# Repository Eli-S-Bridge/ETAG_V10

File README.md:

# ETAG_V10
ETAG arduino code and assembly files for the ETAG RFID reader version 10.

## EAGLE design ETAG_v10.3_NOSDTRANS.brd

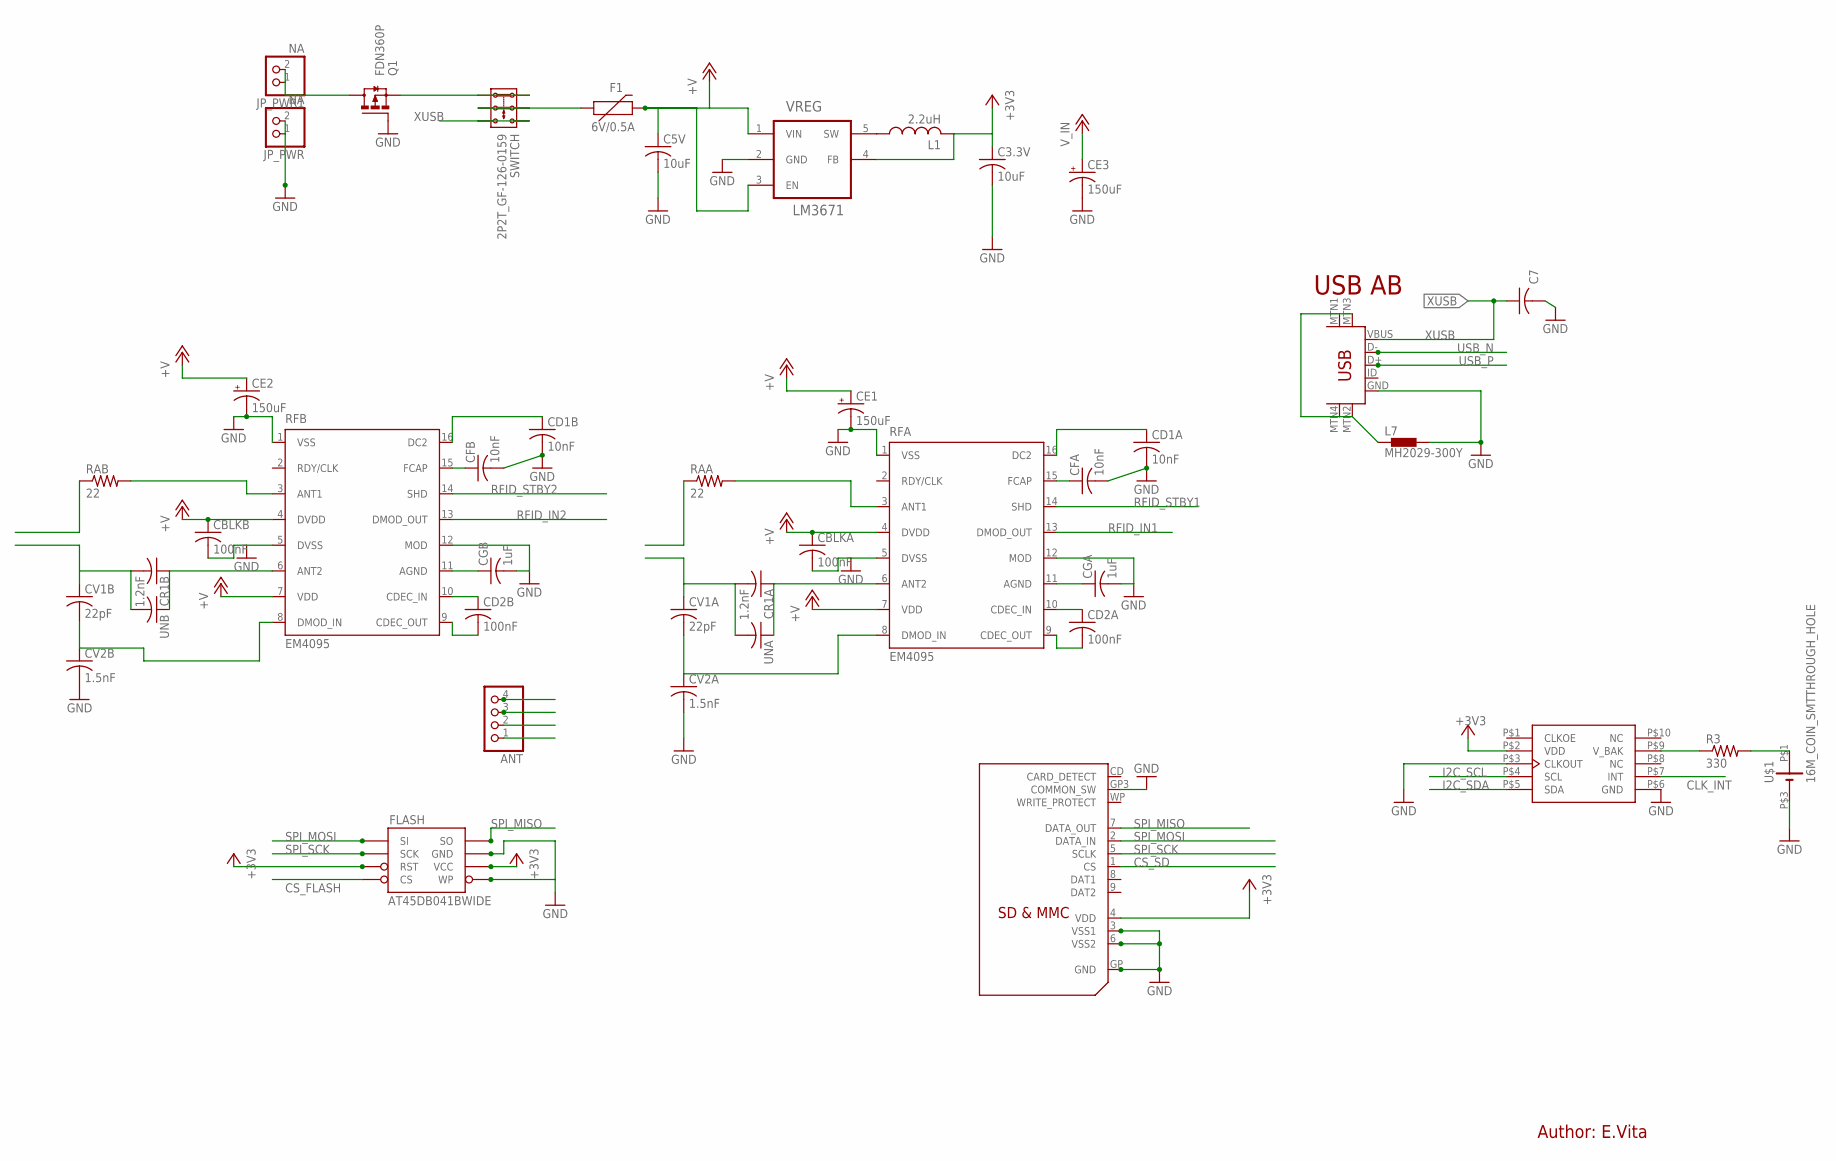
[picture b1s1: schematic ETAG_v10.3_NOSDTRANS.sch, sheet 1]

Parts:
ANT: PINHD-1X4; 1X04
C3.3V, C5V: 10uF; C0805
C7: 10nF; C0603-ROUND
CBLKA: 100nF; C0603-ROUND
CBLKB: 100nF; C0603-ROUND
CD1A, CD1B: 10nF; C0603-ROUND
CD2A, CD2B: 100nF; C0603-ROUND
CE1, CE2, CE3: 150uF; PANASONIC_C
CFA: 10nF; C0603-ROUND
CFB: 10nF; C0603-ROUND
CGA: 1uF; C0603-ROUND
CGB: 1uF; C0603-ROUND
CR1A, CR1B: 1.2nF; C0603-ROUND
CV1A, CV1B: 22pF; C0603-ROUND
CV2A, CV2B: 1.5nF; C0603-ROUND
F1: 6V/0.5A; 1206
FLASH: AT45DB041BWIDE; SO08WIDE
JP_PWR, JP_PWR1: NA; 1X02
L1: 2.2uH; SMT_COIL_INDUCTOR_4X4MM
L7: MH2029-300Y; C0805K
Q1: FDN360P; SUPER-SOT3
R3: 330; C0603-ROUND
RAA: 22; R0805
RAB: 22; R0805
RFA: EM4095; SO16
RFB: EM4095; SO16
RTC: MC-RTC-RV-3029-C3-I2C; MC-RTC-C3_SPECIAL
SD: SDMMC06132; 06132
SWITCH: 2P2T_GF-126-0159
U$1: 16M_COIN_SMTTHROUGH_HOLE; 16_MM_THROUGH_HOLE
UNA: C-US; C0603-ROUND
UNB: C-US; C0603-ROUND
USB: USB-MINIB-5PIN; USB-MINIB
VREG: LM3671; SOT23-5L

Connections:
2GND: L7.1, USB.MTN1 (MTN2), USB.MTN2 (MTN3), USB.MTN3 (MTN1), USB.MTN4
12_IN: JP_PWR1.1, JP_PWR1.2, Q1.3 (D)
+3V3: C3.3V.1, FLASH.3 (RST), FLASH.6 (VCC), L1.P$2 (2), RTC.P$2 (VDD), SD.4 (VDD), VREG.4 (FB); also elsewhere on the board
AANT: ANT.4, RAA.1
BANT: ANT.2, RAB.1
CLK_INT: RTC.P$7 (INT); also elsewhere on the board
CS_FLASH: FLASH.4 (CS); also elsewhere on the board
CS_SD: SD.1 (CS); also elsewhere on the board
CVA: ANT.3, CR1A.2, CV1A.1, UNA.2
CVB: ANT.1, CR1B.2, CV1B.1, UNB.2
GND: C3.3V.2, C5V.2, C7.2, CBLKA.2, CBLKB.2, CD1A.2, CD1B.2, CE1.-, CE2.-, CE3.-, CFA.2, CFB.2, CGA.2, CGB.2, CV2A.2, CV2B.2, FLASH.5 (WP), FLASH.7 (GND), JP_PWR.1, JP_PWR.2, L7.2, Q1.1 (G), RFA.1 (VSS), RFA.5 (DVSS), RFA.12 (MOD), RFB.1 (VSS), RFB.5 (DVSS), RFB.12 (MOD), RTC.P$3 (CLKOUT), RTC.P$6 (GND), SD.3 (VSS1), SD.6 (VSS2), SD.GP (GND), SD.GP3 (COMMON_SW), U$1.P$3 (-), USB.GND, VREG.2 (GND); also elsewhere on the board
I2C_SCL: RTC.P$4 (SCL); also elsewhere on the board
I2C_SDA: RTC.P$5 (SDA); also elsewhere on the board
unnamed: CFB.1, RFB.15 (FCAP)
unnamed: CGB.1, RFB.11 (AGND)
unnamed: CFA.1, RFA.15 (FCAP)
unnamed: CGA.1, RFA.11 (AGND)
unnamed: CD1A.1, RFA.16 (DC2)
unnamed: CR1B.1, RFB.6 (ANT2), UNB.1
unnamed: CV1B.2, CV2B.1, RFB.8 (DMOD_IN)
unnamed: CD1B.1, RFB.16 (DC2)
unnamed: F1.1, SWITCH.P2A (2.1), SWITCH.P2B (2.2)
unnamed: CD2B.2, RFB.9 (CDEC_OUT)
unnamed: CR1A.1, RFA.6 (ANT2), UNA.1
unnamed: CV1A.2, CV2A.1, RFA.8 (DMOD_IN)
unnamed: CD2B.1, RFB.10 (CDEC_IN)
unnamed: RAB.2, RFB.3 (ANT1)
unnamed: Q1.2 (S), SWITCH.P1A (1.1), SWITCH.P1B (1.2)
unnamed: CD2A.2, RFA.9 (CDEC_OUT)
unnamed: CD2A.1, RFA.10 (CDEC_IN)
unnamed: RAA.2, RFA.3 (ANT1)
unnamed: R3.1, RTC.P$9 (V_BAK)
unnamed: R3.2, U$1.P$1 (+)
RFID_IN1: RFA.13 (DMOD_OUT); also elsewhere on the board
RFID_IN2: RFB.13 (DMOD_OUT); also elsewhere on the board
RFID_STBY1: RFA.14 (SHD); also elsewhere on the board
RFID_STBY2: RFB.14 (SHD); also elsewhere on the board
SPI_MISO: FLASH.8 (SO), SD.7 (DATA_OUT); also elsewhere on the board
SPI_MOSI: FLASH.1 (SI), SD.2 (DATA_IN); also elsewhere on the board
SPI_SCK: FLASH.2 (SCK), SD.5 (SCLK); also elsewhere on the board
SW: L1.P$1 (1), VREG.5 (SW)
USB_N: USB.D-; also elsewhere on the board
USB_P: USB.D+; also elsewhere on the board
V_IN: C5V.1, CBLKA.1, CBLKB.1, CE1.+, CE2.+, CE3.+, F1.2, RFA.4 (DVDD), RFA.7 (VDD), RFB.4 (DVDD), RFB.7 (VDD), VREG.1 (VIN), VREG.3 (EN); also elsewhere on the board
XUSB: C7.1, SWITCH.P3A (3.1), SWITCH.P3B (3.2), USB.VBUS

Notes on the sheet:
USB AB
Author: E.Vita

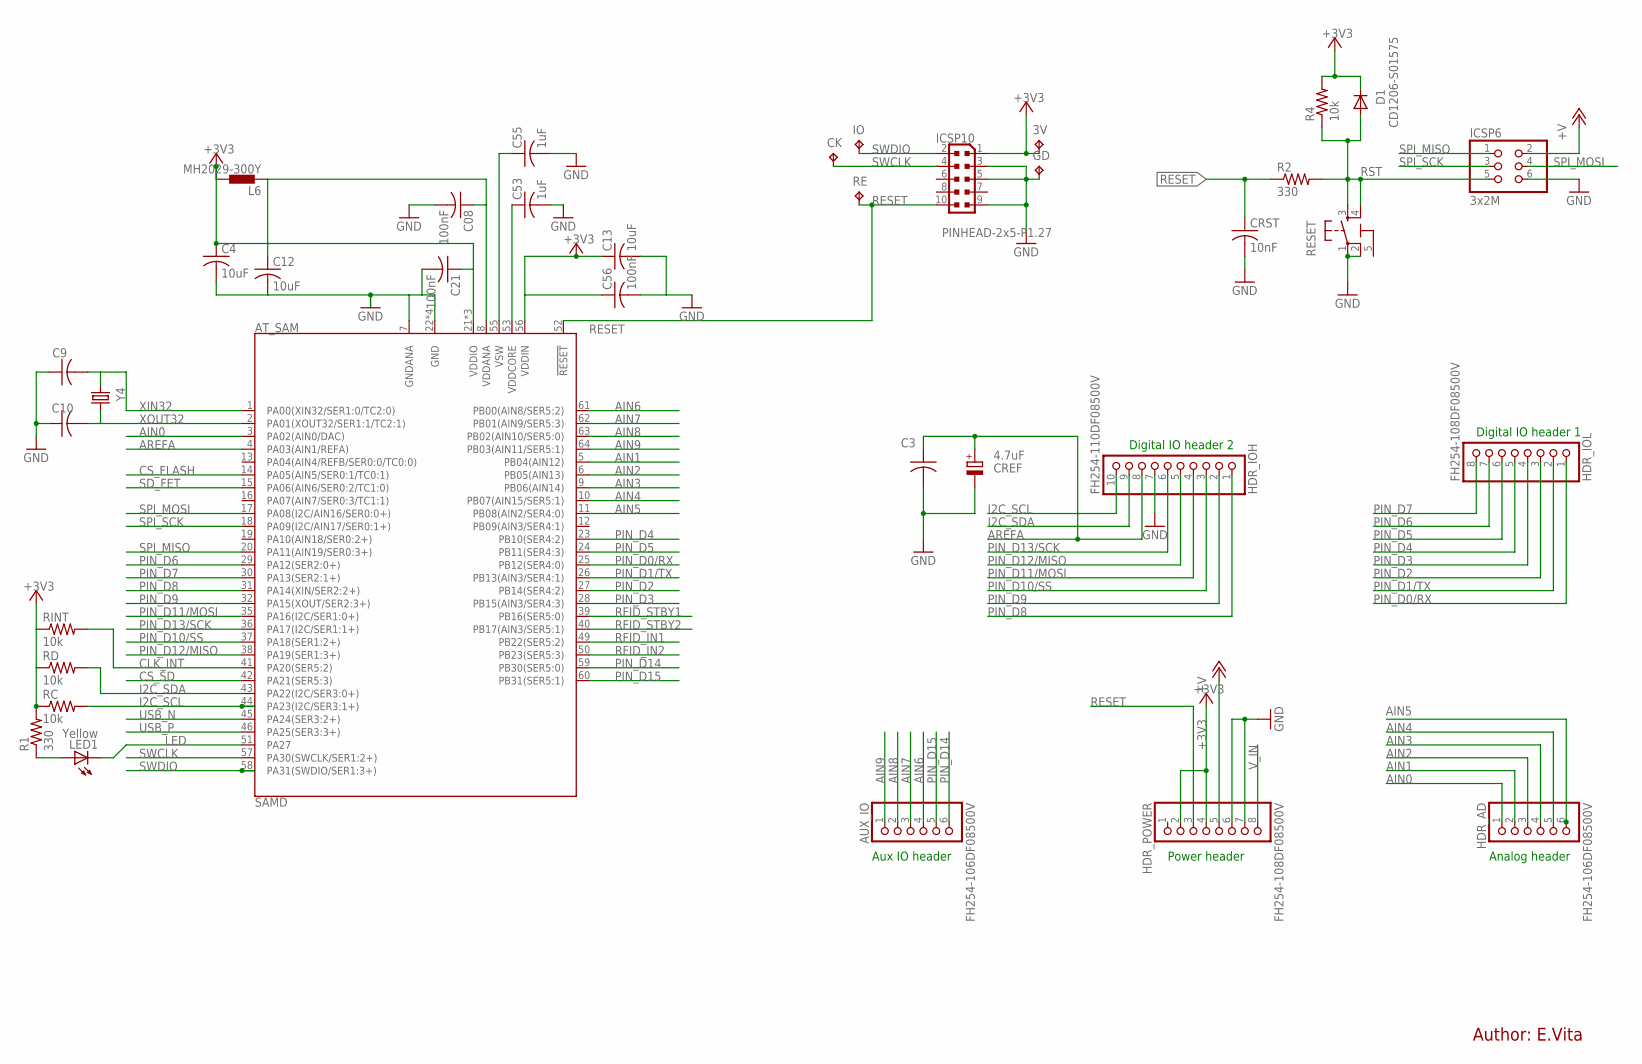
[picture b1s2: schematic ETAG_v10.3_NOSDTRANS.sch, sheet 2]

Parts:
3V: TPTP12R; TP12R
AT_SAM: SAMD; TQFP_10MM_0.5PITCH
AUX_IO: FH254-106DF08500V; 1X06
C3, C08, C21, C56: 100nF; C0603-ROUND
C4, C12, C13: 10uF; C0805
C9, C10: 22pF; C0603-ROUND
C53, C55: 1uF; C0603-ROUND
CK: TPTP12R; TP12R
CREF: 4.7uF; SMC_A
CRST: 10nF; C0603-ROUND
D1: CD1206-S01575; MINIMELF
GD: TPTP12R; TP12R
HDR_AD: FH254-106DF08500V; 1X06
HDR_IOH: FH254-110DF08500V; 1X10
HDR_IOL: FH254-108DF08500V; 1X08
HDR_POWER: FH254-108DF08500V; 1X08
ICSP6: 3x2M; 2X03
ICSP10: PINHEAD-2x5-P1.27; PINHEAD_2X05_127
IO: TPTP12R; TP12R
L6: MH2029-300Y; C0805K
LED1: Yellow; CHIPLED_0805
R1, R2: 330; C0603-ROUND
R4: 10k; C0603-ROUND
RC: 10k; C0603-ROUND
RD: 10k; C0603-ROUND
RE: TPTP12R; TP12R
RESET: TS42031-160R-TR-7260; TS42
RINT: 10k; C0603-ROUND
Y4: 32,768Khz; RESONATOR_EPSON_FC_145

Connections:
5-GND: RESET.5 (5-GND)
+3V3: 3V.TP, AT_SAM.21 (VDDIO), AT_SAM.34 (VDDIO), AT_SAM.48 (VDDIO), AT_SAM.56 (VDDIN), C4.1, C13.1, C21.1, C56.1, D1.C, HDR_POWER.2, HDR_POWER.4, ICSP10.1, L6.2, R1.2, R4.2, RC.1, RD.1, RINT.1; also elsewhere on the board
AIN0: AT_SAM.3 (PA02(AIN0/DAC)), HDR_AD.1
AIN1: AT_SAM.5 (PB04(AIN12)), HDR_AD.2
AIN2: AT_SAM.6 (PB05(AIN13)), HDR_AD.3
AIN3: AT_SAM.9 (PB06(AIN14)), HDR_AD.4
AIN4: AT_SAM.10 (PB07(AIN15/SER5:1)), HDR_AD.5
AIN5: AT_SAM.11 (PB08(AIN2/SER4:0)), HDR_AD.6
AIN6: AT_SAM.61 (PB00(AIN8/SER5:2)), AUX_IO.4
AIN7: AT_SAM.62 (PB01(AIN9/SER5:3)), AUX_IO.3
AIN8: AT_SAM.63 (PB02(AIN10/SER5:0)), AUX_IO.2
AIN9: AT_SAM.64 (PB03(AIN11/SER5:1)), AUX_IO.1
AREFA: AT_SAM.4 (PA03(AIN1/REFA)), C3.1, CREF.+, HDR_IOH.8
CLK_INT: AT_SAM.41 (PA20(SER5:2)), RINT.2; also elsewhere on the board
CS_FLASH: AT_SAM.14 (PA05(AIN5/SER0:1/TC0:1)); also elsewhere on the board
CS_SD: AT_SAM.42 (PA21(SER5:3)); also elsewhere on the board
GND: AT_SAM.7 (GNDANA), AT_SAM.22 (GND), AT_SAM.33 (GND), AT_SAM.47 (GND), AT_SAM.54 (GND), C3.2, C4.2, C08.2, C9.1, C10.1, C12.2, C13.2, C21.2, C53.2, C55.2, C56.2, CREF.-, CRST.2, GD.TP, HDR_IOH.7, HDR_POWER.6, HDR_POWER.7, ICSP6.6, ICSP10.3, ICSP10.5, ICSP10.9, RESET.1, RESET.2; also elsewhere on the board
I2C_SCL: AT_SAM.44 (PA23(I2C/SER3:1+)), HDR_IOH.10, RC.2; also elsewhere on the board
I2C_SDA: AT_SAM.43 (PA22(I2C/SER3:0+)), HDR_IOH.9, RD.2; also elsewhere on the board
LED: AT_SAM.51 (PA27), LED1.C
unnamed: LED1.A, R1.1
unnamed: AT_SAM.53 (VDDCORE), C53.1
unnamed: AT_SAM.55 (VSW), C55.1
PIN_D0/RX: AT_SAM.25 (PB12(SER4:0)), HDR_IOL.1
PIN_D1/TX: AT_SAM.26 (PB13(AIN3/SER4:1)), HDR_IOL.2
PIN_D2: AT_SAM.27 (PB14(SER4:2)), HDR_IOL.3
PIN_D3: AT_SAM.28 (PB15(AIN3/SER4:3)), HDR_IOL.4
PIN_D4: AT_SAM.23 (PB10(SER4:2)), HDR_IOL.5
PIN_D5: AT_SAM.24 (PB11(SER4:3)), HDR_IOL.6
PIN_D6: AT_SAM.29 (PA12(SER2:0+)), HDR_IOL.7
PIN_D7: AT_SAM.30 (PA13(SER2:1+)), HDR_IOL.8
PIN_D8: AT_SAM.31 (PA14(XIN/SER2:2+)), HDR_IOH.1
PIN_D9: AT_SAM.32 (PA15(XOUT/SER2:3+)), HDR_IOH.2
PIN_D10/SS: AT_SAM.37 (PA18(SER1:2+)), HDR_IOH.3
PIN_D11/MOSI: AT_SAM.35 (PA16(I2C/SER1:0+)), HDR_IOH.4
PIN_D12/MISO: AT_SAM.38 (PA19(SER1:3+)), HDR_IOH.5
PIN_D13/SCK: AT_SAM.36 (PA17(I2C/SER1:1+)), HDR_IOH.6
PIN_D14: AT_SAM.59 (PB30(SER5:0)), AUX_IO.6
PIN_D15: AT_SAM.60 (PB31(SER5:1)), AUX_IO.5
RESET: AT_SAM.52 (!RESET!), CRST.1, HDR_POWER.3, ICSP10.10, R2.1, RE.TP
RFID_IN1: AT_SAM.49 (PB22(SER5:2)); also elsewhere on the board
RFID_IN2: AT_SAM.50 (PB23(SER5:3)); also elsewhere on the board
RFID_STBY1: AT_SAM.39 (PB16(SER5:0)); also elsewhere on the board
RFID_STBY2: AT_SAM.40 (PB17(AIN3/SER5:1)); also elsewhere on the board
RST: D1.A, ICSP6.5, R2.2, R4.1, RESET.3, RESET.4
SD_FET: AT_SAM.15 (PA06(AIN6/SER0:2/TC1:0))
SPI_MISO: AT_SAM.20 (PA11(AIN19/SER0:3+)), ICSP6.1; also elsewhere on the board
SPI_MOSI: AT_SAM.17 (PA08(I2C/AIN16/SER0:0+)), ICSP6.4; also elsewhere on the board
SPI_SCK: AT_SAM.18 (PA09(I2C/AIN17/SER0:1+)), ICSP6.3; also elsewhere on the board
SWCLK: AT_SAM.57 (PA30(SWCLK/SER1:2+)), CK.TP, ICSP10.4
SWDIO: AT_SAM.58 (PA31(SWDIO/SER1:3+)), ICSP10.2, IO.TP
USB_N: AT_SAM.45 (PA24(SER3:2+)); also elsewhere on the board
USB_P: AT_SAM.46 (PA25(SER3:3+)); also elsewhere on the board
VDDANA: AT_SAM.8 (VDDANA), C08.1, C12.1, L6.1
V_IN: HDR_POWER.5, HDR_POWER.8, ICSP6.2; also elsewhere on the board
XIN32: AT_SAM.1 (PA00(XIN32/SER1:0/TC2:0)), C9.2, Y4.P$1 (1)
XOUT32: AT_SAM.2 (PA01(XOUT32/SER1:1/TC2:1)), C10.2, Y4.P$2 (2)

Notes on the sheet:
Author: E.Vita
Digital IO header 2
Digital IO header 1
Analog header
Power header
Aux IO header

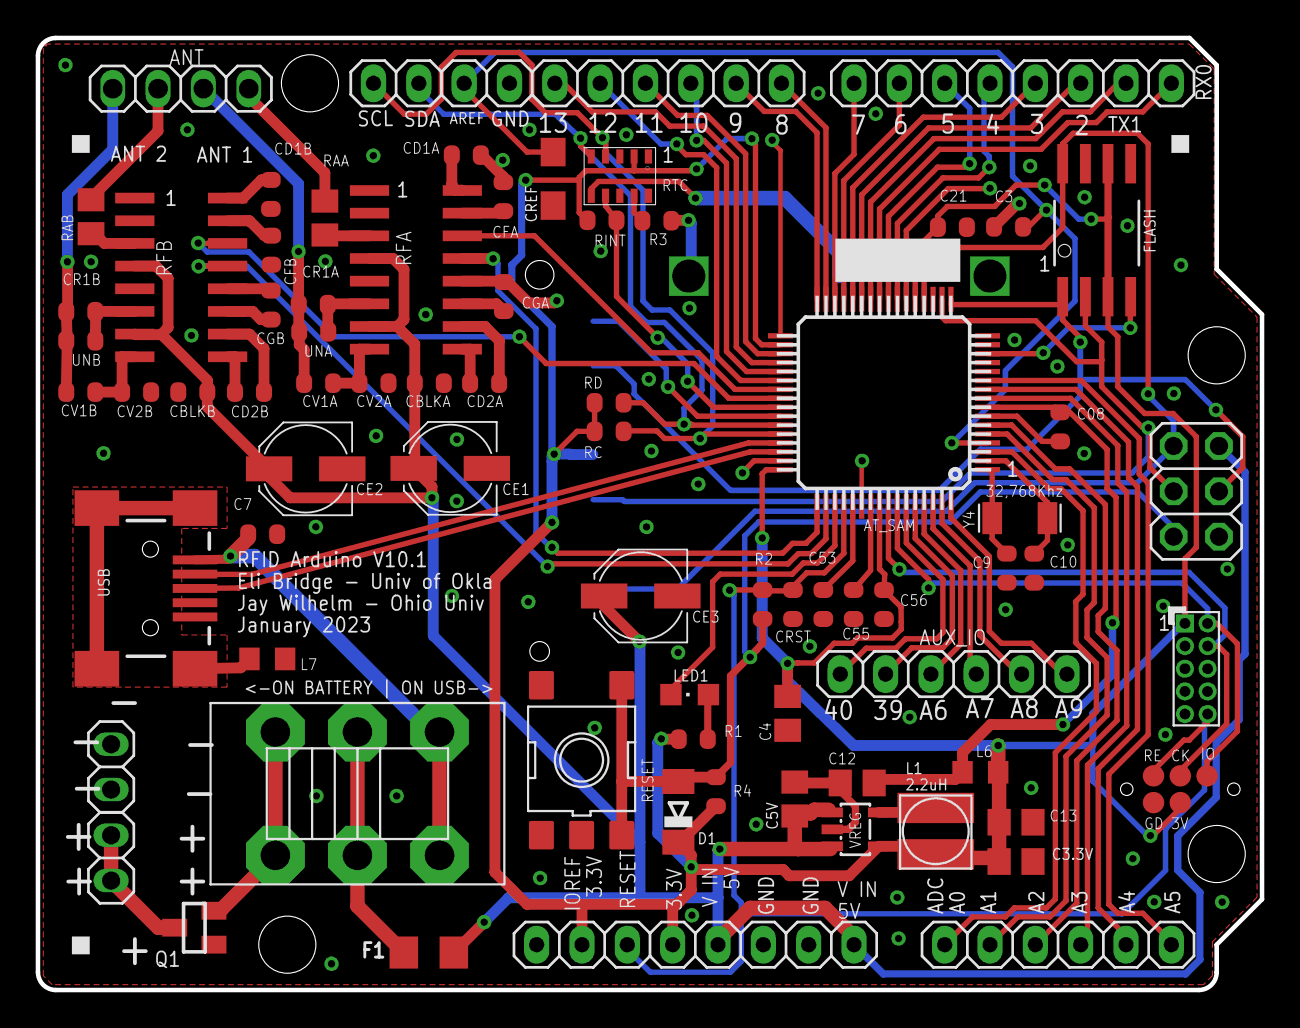
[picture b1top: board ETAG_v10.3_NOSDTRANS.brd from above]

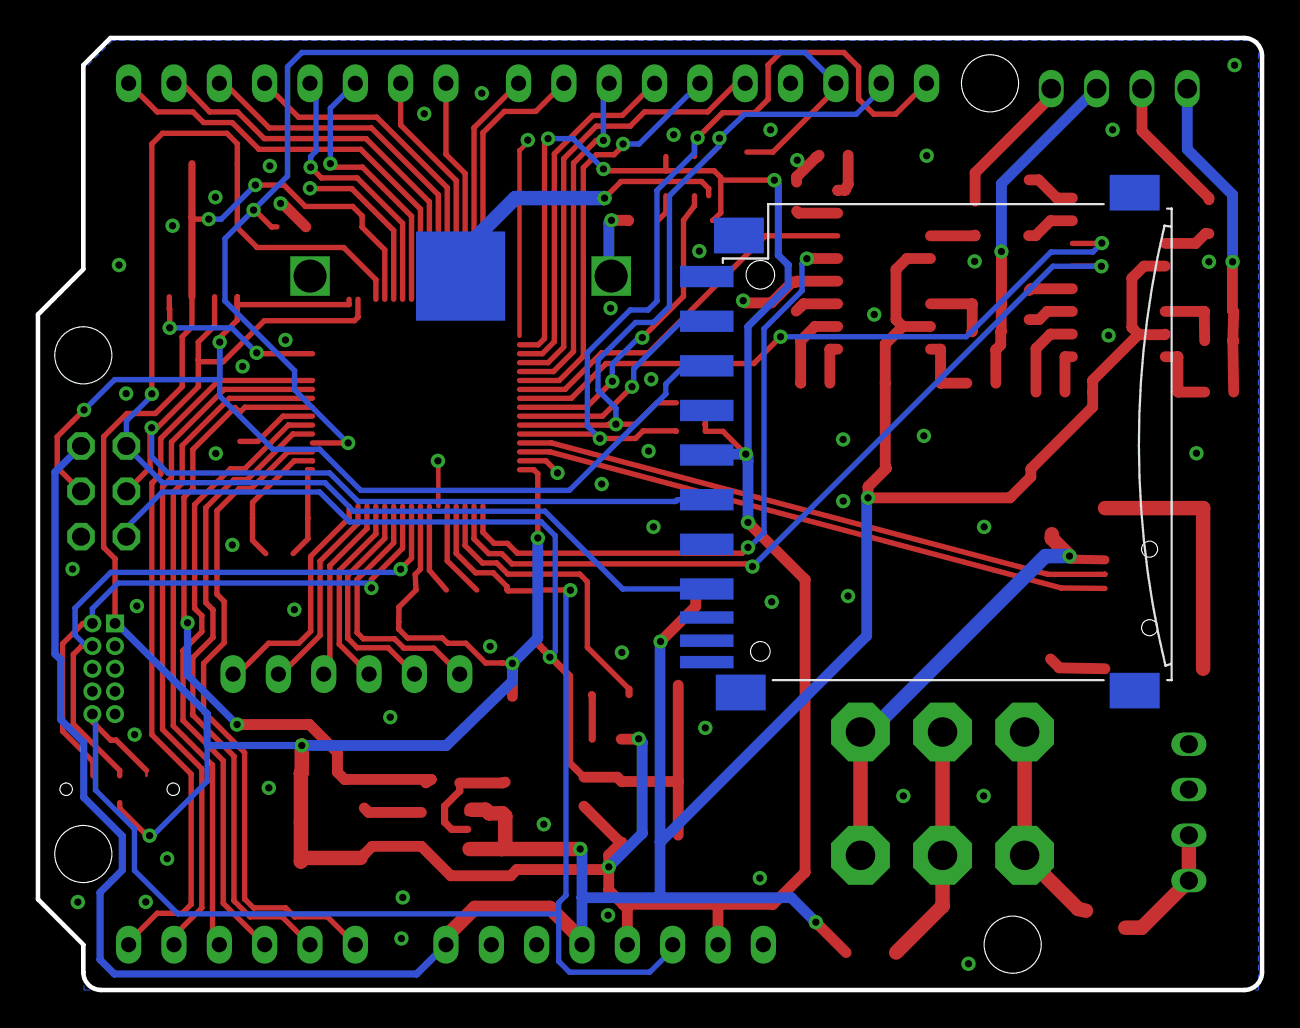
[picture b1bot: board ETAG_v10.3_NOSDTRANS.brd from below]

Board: 4 copper layers, 68.6 x 53.3 mm, 83 parts (2 on the bottom side), 83 nets.

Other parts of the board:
U$2, U$3, U$4: SQUARE-1MM-3R

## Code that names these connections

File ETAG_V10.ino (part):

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  Adesto® AT45DB321E
  34,603,008 bits of memory are organized as 8,192 pages of 528 bytes each.
  there is a 23-bit address sequence:
    The first 13 bits (PA12 - PA0) specify the page.
    The last 10 bits (BA9 - BA0) specify the byte address within the page.
  Data can be written/erased as pages, blocks (8 pages) or sectors (usually 128 pages).
  The First sector is pages 0-7; others are much larger
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#define serial SerialUSB       // Designate the USB connection as the primary serial comm port - note lowercase "serial"
#define SD_FAT_TYPE         3  // Type 3 Reads all card formats
#define SPI_SPEED          SD_SCK_MHZ(4) .  //Finds fastest speed.
//#define DEMOD_OUT_1      41  // (PB22) this is the target pin for the raw RFID data from RF circuit 1
//#define DEMOD_OUT_2      42  // (PB23) this is the target pin for the raw RFID data from RF circuit 2
//#define SHD_PINA         48  // (PB16) Setting this pin high activates RFID circuit 1
//#define SHD_PINB         49  // (PB17) Setting this pin high activates RFID circuit 2
#define SDselect           46  // (PA21) Chip select for SD card. Make this pin low to activate the SD card for SPI communication
#define SDon               45  // (PA06) Provides power to the SD via a high side mosfet. Make this pin low to power on the SD card
#define FlashCS            44  // (PA05) Chip select for flash memory. Make this pin low to activate the flash memory for SPI communication
#define LED_RFID           43  // (PA27) Pin to control the LED indicator.
#define INT1               47  // (PA20) Clock interrupt for alarms and timers on the RTC
#define MOTR               2   // used for sleep function (need to investigate this). 
RV3129 rtc;   //Initialize an instance for the RV3129 real time clock library.

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
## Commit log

2019-10-23 Initial upload
    Version 10 script. Uses built in SD library (may want to switch to SDfat later)
2019-11-11 Added flash-only logging mode
    Two logging modes now possible - Flash only and traditional (SD+Flash). Also this code does not use an address pointer for the Flash memory. On startup the last flash address is located and the addre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
2019-11-11 Added board assembly files
    Added eagle files and gerbers
2019-11-16 Added assembly files and pics
    Added gerbers and BOM spreadsheet. Also pics of PCB array and finished boards
2019-11-16 pixed pic
2019-11-16 Create Bootloader.zip
    included Bootloader
2020-01-28 date bug fixed
    Day and year were reversed on dates written to SD card. Now fixed
2023-03-16 Added IOS tags
    Mar 2023 - simplified Flash memory writing - one write command and one read command that automatically writes across pages.
    - Added ISO11784/5 tag reading capability and temperature tags!!!! set global ISO variable to 1 for ISO tags.
    - Progressed toward elimination of string variables (still some strings used with the real time clock)
    - revamped SD card storage functions
    - enabled log files for both SD and Flash logging modes
    - Revamped file storage. New file created for each data transfer.
2023-03-25 Update ETAG_V10.ino
    fixed frame error on logged date
2023-03-26 Manual Update
    Manual Update
2023-04-04 Bugfix_Apr4_2023
    Fixed bug that saved dates as 0s to SD card
2023-04-04 altered menu
    Made menu accessible when logging.
2023-05-10 updated manual
2023-09-12 New data logging scheme
    Updates to SD card now involve matching up data lines to prevent writing duplicated data
2023-09-12 new logging scheme
    turned off wake and sleep times to
2023-09-15 New logging scheme
    Updated manual and some code annotation.
2023-09-15 new logging scheme
    Fixed manual formatting
2024-05-21 updated manual
    Fixed some inaccuracies in the manual.
2024-06-11 updated hardware files
    Finally put the new board file up. (v10.3)
2026-01-21 Revised Sleep function
    Found a set of sleep parameters that preserves functioning in ISO mode
2026-02-06 Major Update - new menu and sleep modes
    Major Update - new menu setup that allows for parameter setting without reprogramming. updated sleepn to work with ISO mode. Also manual has been updated, but still need Arduino 2 and windows 11 upda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
2026-04-14 Update Gen3_RFID_Manual_V10.pdf
    More manual updates

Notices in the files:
ETAG_V10.ino:
Licenced in the public domain
parts and their libraries:
SparkFun-DigitalIC: Licensing: Creative Commons ShareAlike 4.0 International - https://creativecommons.org/licenses/by-sa/4.0
